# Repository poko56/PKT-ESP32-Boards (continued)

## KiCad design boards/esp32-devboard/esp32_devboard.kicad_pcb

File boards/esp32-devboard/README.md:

<h1 align="center">ESP32 Dev Board</h1>

<p align="center">บอร์ดพัฒนา ESP32-WROOM-32E ขนาด 29 × 54.6 มม. เสียบ breadboard ได้</p>

## บอร์ดนี้คืออะไร

บอร์ดพัฒนาทั่วไปสำหรับเรียนรู้ ทดลอง และทำต้นแบบ เสียบ USB-C แล้วอัปโหลดโค้ดได้เลย
เพราะมีวงจร auto-reset ไม่ต้องกดปุ่มเอง

## เหมาะกับงานแบบไหน

- เรียนรู้ ESP32 ด้วย Arduino หรือ PlatformIO
- ทำต้นแบบ IoT, Wi-Fi และ Bluetooth
- ใช้สอนในห้องเรียนหรือเวิร์กช็อป

## สเปก

| รายการ | ค่า |
|---|---|
| ขนาด | 29 × 54.6 มม. PCB 2 ชั้น |
| โมดูล | ESP32-WROOM-32E |
| USB | USB-C ผ่าน CH340C พร้อม auto-reset |
| ไฟเลี้ยง | 5V ผ่าน SS14 และ AMS1117-3.3 |
| ปุ่มและไฟ | EN, BOOT, LED PWR, LED IO2 |
| ขา I/O | header 17 ขา 2 แถว ห่างกัน 25.4 มม. |

## วงจร

ดูแบบซูมได้ที่ [schematic.pdf](docs/schematic.pdf)

> สถานะ: มี Gerber ใน [`fab/`](fab) ไม่มี DRC error แต่ยังไม่ได้ทดสอบกับบอร์ดจริง
> ERC มี error 1 รายการโดยตั้งใจ จากขา V3 ของ CH340C ที่ต่อกับ VCC ตาม datasheet

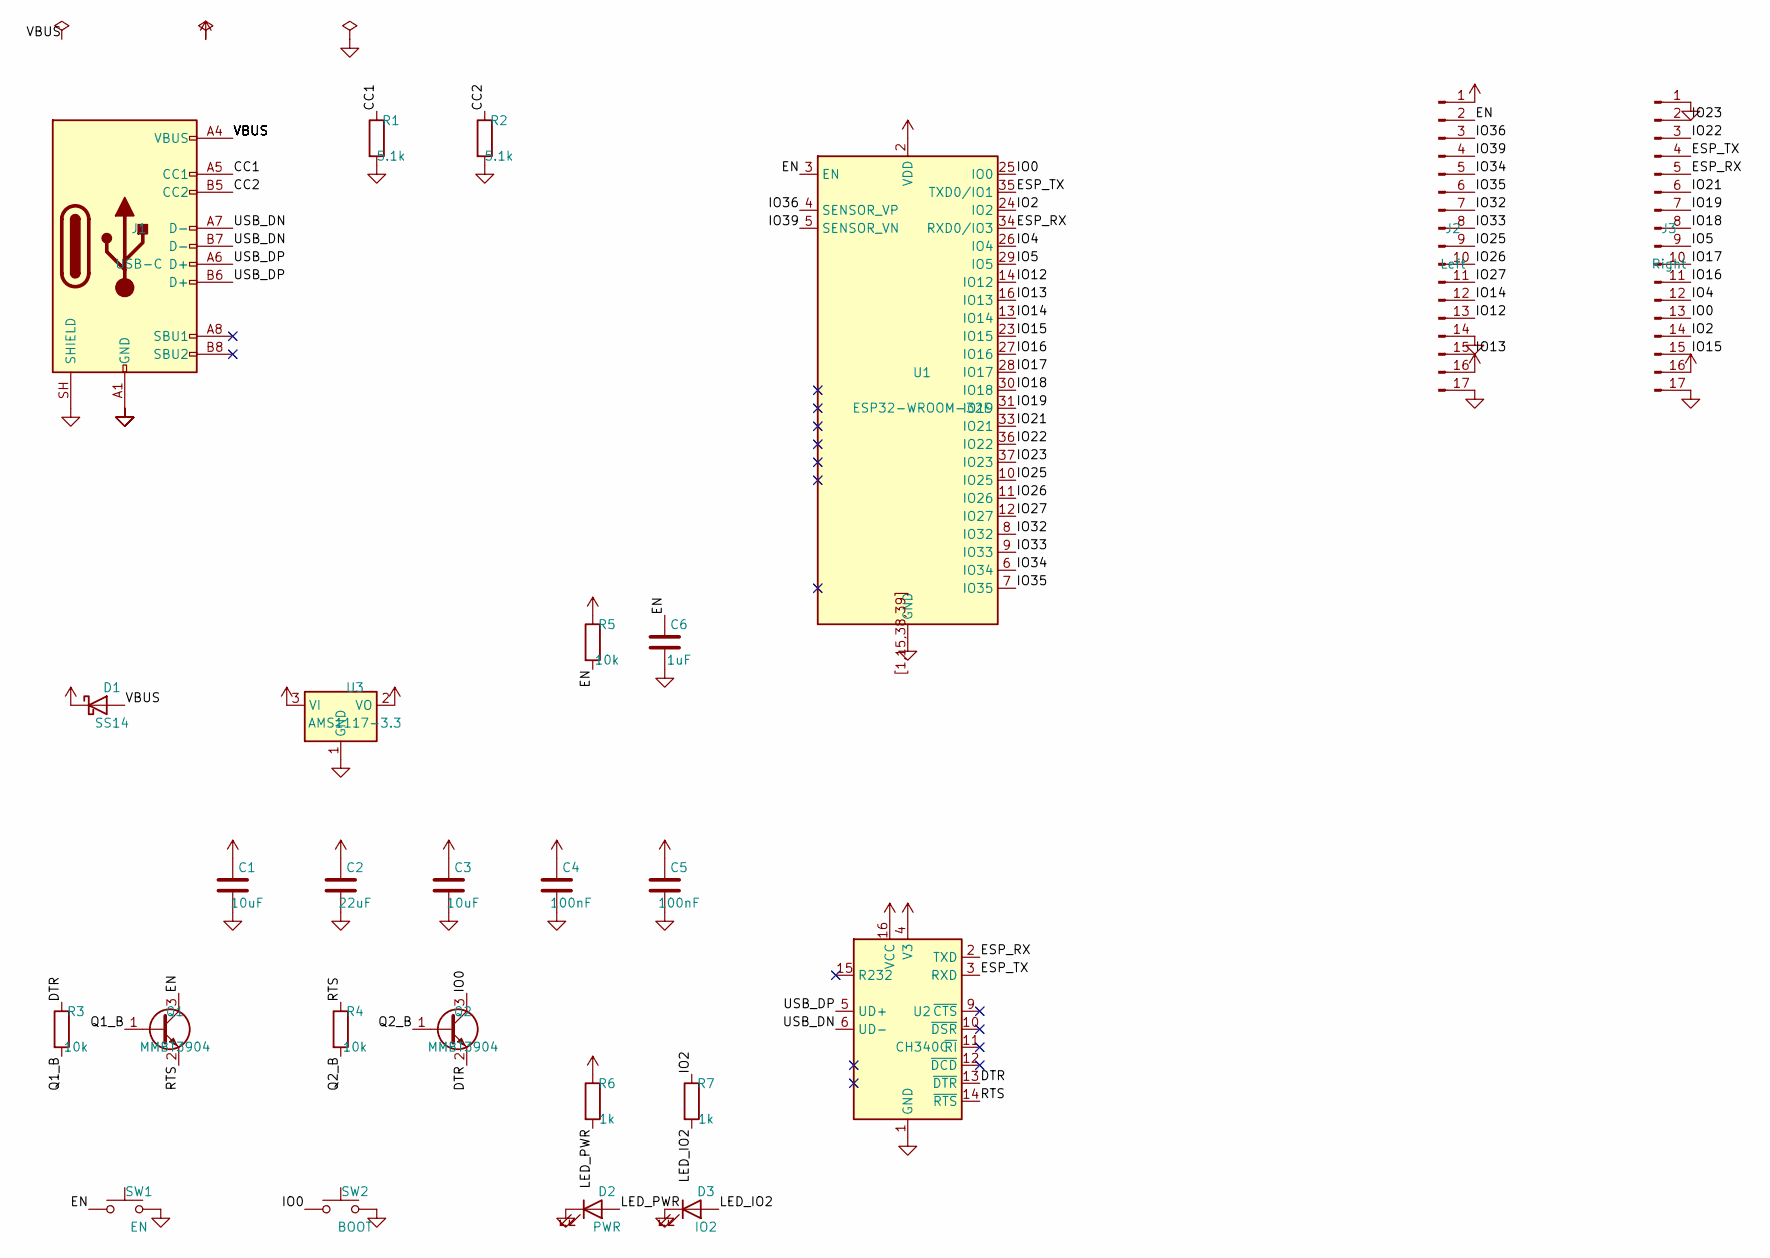
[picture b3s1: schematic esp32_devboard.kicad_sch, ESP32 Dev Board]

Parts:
C1: 10uF; C_0805_2012Metric; MPN 10uF 16V X7R 0805
C2: 22uF; C_0805_2012Metric; MPN 22uF 10V X5R 0805
C3: 10uF; C_0603_1608Metric; MPN 10uF 10V X5R 0603
C4, C5: 100nF; C_0603_1608Metric; MPN 100nF 16V X7R 0603
C6: 1uF; C_0603_1608Metric; MPN 1uF 16V X7R 0603
D1: SS14; D_SMA; MPN SS14
D2: PWR; LED_0603_1608Metric; MPN LED 0603 red
D3: IO2; LED_0603_1608Metric; MPN LED 0603 blue
J1: USB-C; USB_C_Receptacle_HRO_TYPE-C-31-M-12; MPN HRO TYPE-C-31-M-12
J2: Left; PinHeader_1x17_P2.54mm_Vertical; MPN 2.54mm 1x17 header
J3: Right; PinHeader_1x17_P2.54mm_Vertical; MPN 2.54mm 1x17 header
Q1, Q2: MMBT3904; SOT-23; MPN MMBT3904
R1, R2: 5.1k; R_0603_1608Metric; MPN 5.1k 1% 0603
R3, R4, R5: 10k; R_0603_1608Metric; MPN 10k 1% 0603
R6, R7: 1k; R_0603_1608Metric; MPN 1k 1% 0603
SW1: EN; SW_Push_1P1T_NO_CK_KMR2; MPN CK KMR2
SW2: BOOT; SW_Push_1P1T_NO_CK_KMR2; MPN CK KMR2
U1: ESP32-WROOM-32E; MPN ESP32-WROOM-32E-N4
U2: CH340C; SOIC-16_3.9x9.9mm_P1.27mm; MPN CH340C
U3: AMS1117-3.3; SOT-223-3_TabPin2; MPN AMS1117-3.3

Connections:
+3V3: C2.1, C3.1, C4.1, C5.1, J2.1, J3.16, R5.1, R6.1, U1.2 (VDD), U2.4 (V3), U2.16 (VCC), U3.2 (VO)
+5V: C1.1, D1.1 (K), J2.16, U3.3 (VI)
/CC1: J1.A5 (CC1), R1.1
/CC2: J1.B5 (CC2), R2.1
/DTR: Q2.2 (E), R3.1, U2.13 (~DTR)
/EN: C6.1, J2.2, Q1.3 (C), R5.2, SW1.1, U1.3 (EN)
/ESP_RX: J3.5, U1.34 (RXD0/IO3), U2.2 (TXD)
/ESP_TX: J3.4, U1.35 (TXD0/IO1), U2.3 (RXD)
/IO0: J3.13, Q2.3 (C), SW2.1, U1.25 (IO0)
/IO2: J3.14, R7.1, U1.24 (IO2)
/IO4: J3.12, U1.26 (IO4)
/IO5: J3.9, U1.29 (IO5)
/IO12: J2.13, U1.14 (IO12)
/IO13: J2.15, U1.16 (IO13)
/IO14: J2.12, U1.13 (IO14)
/IO15: J3.15, U1.23 (IO15)
/IO16: J3.11, U1.27 (IO16)
/IO17: J3.10, U1.28 (IO17)
/IO18: J3.8, U1.30 (IO18)
/IO19: J3.7, U1.31 (IO19)
/IO21: J3.6, U1.33 (IO21)
/IO22: J3.3, U1.36 (IO22)
/IO23: J3.2, U1.37 (IO23)
/IO25: J2.9, U1.10 (IO25)
/IO26: J2.10, U1.11 (IO26)
/IO27: J2.11, U1.12 (IO27)
/IO32: J2.7, U1.8 (IO32)
/IO33: J2.8, U1.9 (IO33)
/IO34: J2.5, U1.6 (IO34)
/IO35: J2.6, U1.7 (IO35)
/IO36: J2.3, U1.4 (SENSOR_VP)
/IO39: J2.4, U1.5 (SENSOR_VN)
/LED_IO2: D3.2 (A), R7.2
/LED_PWR: D2.2 (A), R6.2
/Q1_B: Q1.1 (B), R3.2
/Q2_B: Q2.1 (B), R4.2
/RTS: Q1.2 (E), R4.1, U2.14 (~RTS)
/USB_DN: J1.A7 (D-), J1.B7 (D-), U2.6 (UD-)
/USB_DP: J1.A6 (D+), J1.B6 (D+), U2.5 (UD+)
/VBUS: D1.2 (A), J1.A4 (VBUS), J1.A9 (VBUS), J1.B4 (VBUS), J1.B9 (VBUS)
GND: C1.2, C2.2, C3.2, C4.2, C5.2, C6.2, D2.1 (K), D3.1 (K), J1.A1 (GND), J1.A12 (GND), J1.B1 (GND), J1.B12 (GND), J1.SH (SHIELD), J2.14, J2.17, J3.1, J3.17, R1.2, R2.2, SW1.2, SW2.2, U1.1, U1.15, U1.38, U1.39, U1.[1,15,38,39] (GND), U2.1 (GND), U3.1 (GND)

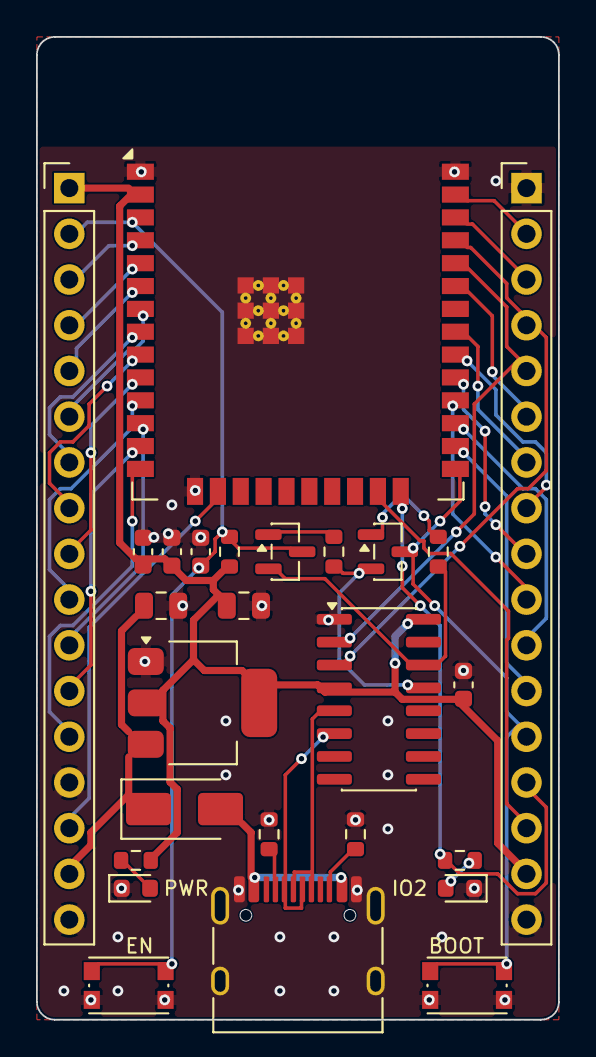
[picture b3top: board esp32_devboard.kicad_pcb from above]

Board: 2 copper layers, 29.0 x 54.6 mm, 26 parts (0 on the bottom side), 41 nets.

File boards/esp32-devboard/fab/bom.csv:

Qty,Designators,Value,Footprint,Part
1,C1,10uF,C_0805_2012Metric,10uF 16V X7R 0805
1,C2,22uF,C_0805_2012Metric,22uF 10V X5R 0805
1,C3,10uF,C_0603_1608Metric,10uF 10V X5R 0603
2,C4 C5,100nF,C_0603_1608Metric,100nF 16V X7R 0603
1,C6,1uF,C_0603_1608Metric,1uF 16V X7R 0603
1,D1,SS14,D_SMA,SS14
1,D2,PWR,LED_0603_1608Metric,LED 0603 red
1,D3,IO2,LED_0603_1608Metric,LED 0603 blue
1,J1,USB-C,USB_C_Receptacle_HRO_TYPE-C-31-M-12,HRO TYPE-C-31-M-12
1,J2,Left,PinHeader_1x17_P2.54mm_Vertical,2.54mm 1x17 header
1,J3,Right,PinHeader_1x17_P2.54mm_Vertical,2.54mm 1x17 header
2,Q1 Q2,MMBT3904,SOT-23,MMBT3904
2,R1 R2,5.1k,R_0603_1608Metric,5.1k 1% 0603
3,R3 R4 R5,10k,R_0603_1608Metric,10k 1% 0603
2,R6 R7,1k,R_0603_1608Metric,1k 1% 0603
1,SW1,EN,SW_Push_1P1T_NO_CK_KMR2,CK KMR2
1,SW2,BOOT,SW_Push_1P1T_NO_CK_KMR2,CK KMR2
1,U1,ESP32-WROOM-32E,ESP32-WROOM-32E,ESP32-WROOM-32E-N4
1,U2,CH340C,SOIC-16_3.9x9.9mm_P1.27mm,CH340C
1,U3,AMS1117-3.3,SOT-223-3_TabPin2,AMS1117-3.3
